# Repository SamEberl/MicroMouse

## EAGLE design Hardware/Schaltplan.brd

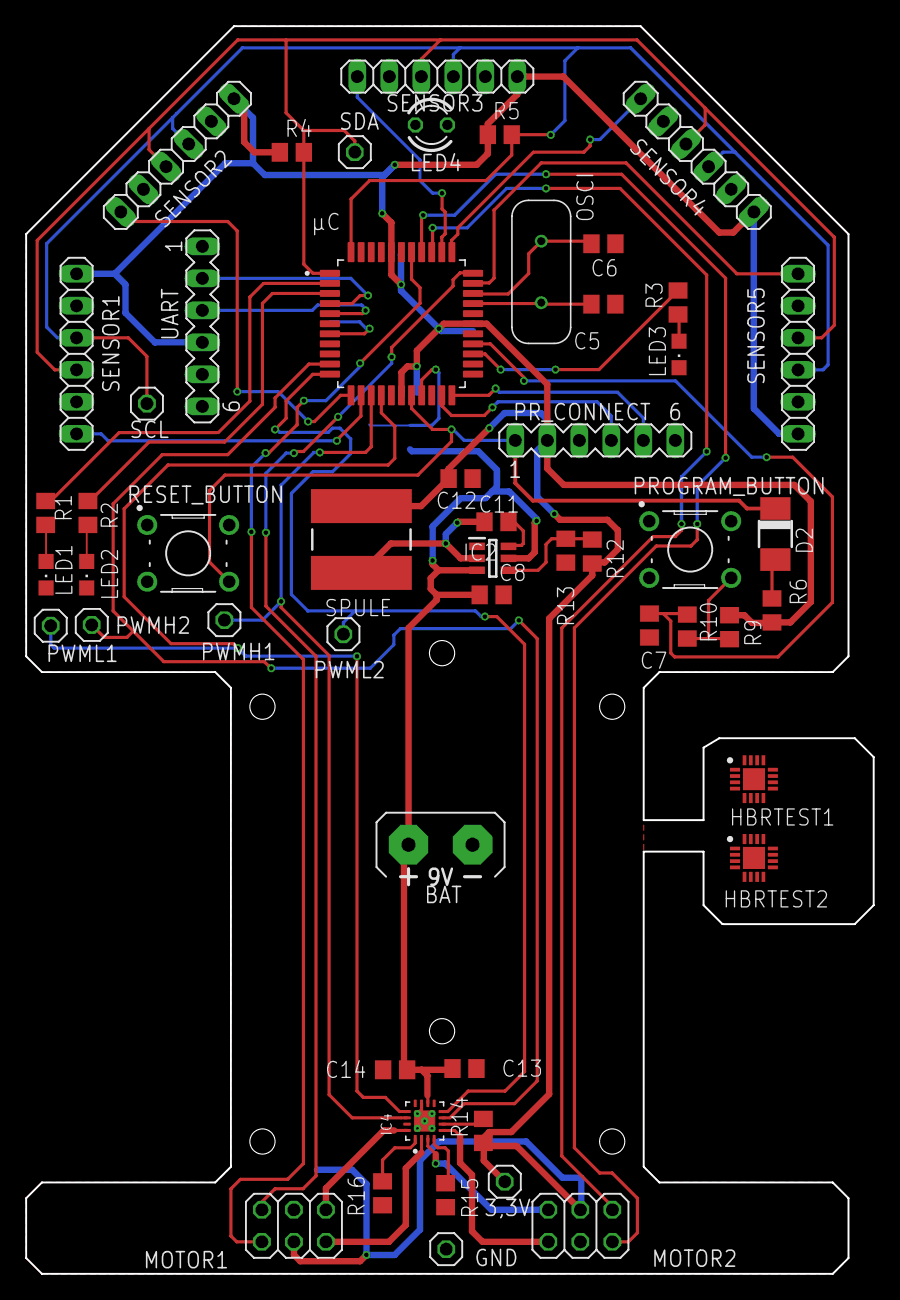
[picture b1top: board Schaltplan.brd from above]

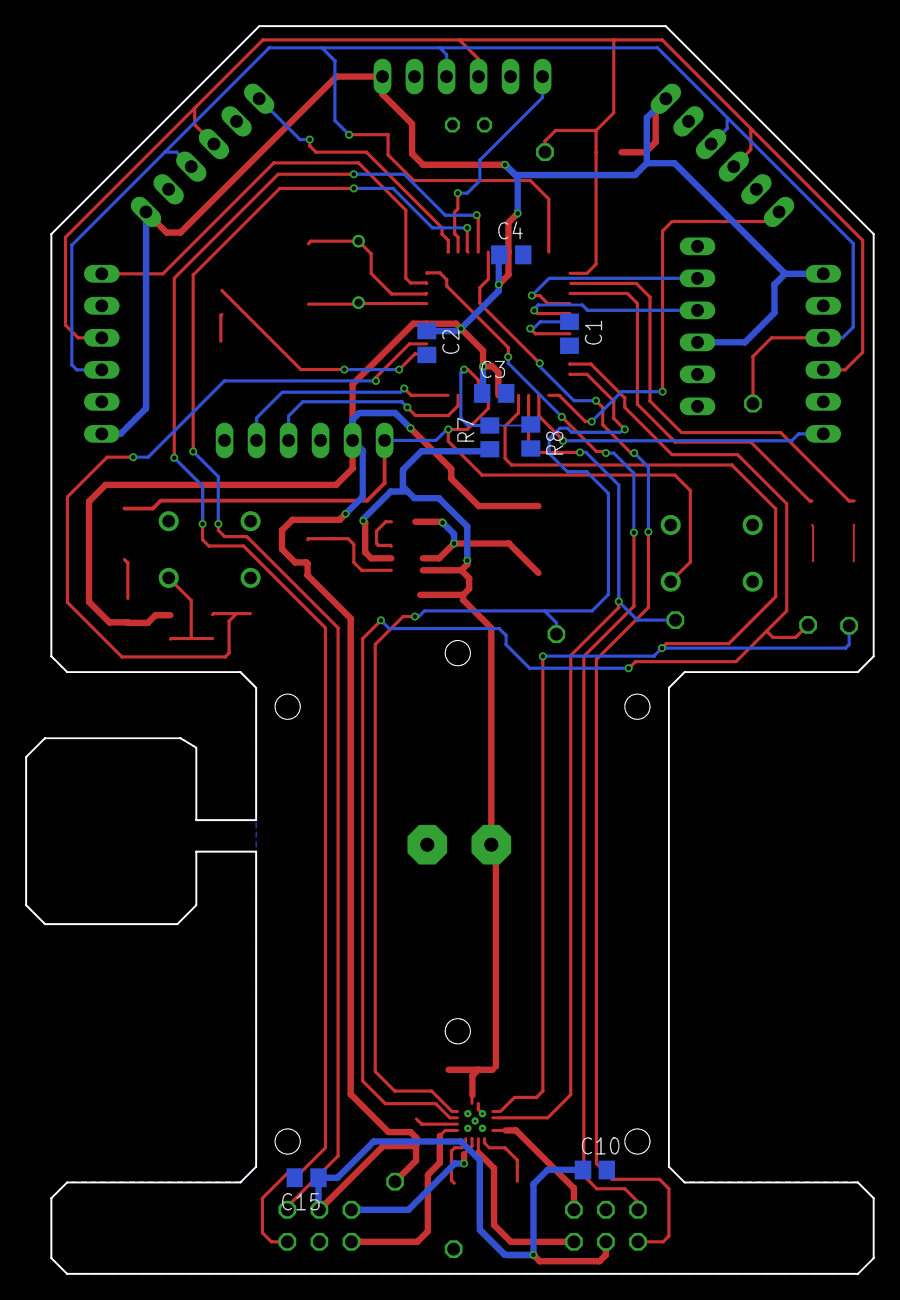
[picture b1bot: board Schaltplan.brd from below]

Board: 2 copper layers, 67.2 x 99.0 mm, 61 parts (8 on the bottom side), 46 nets.

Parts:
3,3V: 1X01
BAT: AB9V
C1: 10μ; C0805
C2, C3, C4: 0,1 μF; C0805
C5, C6: 15pf; C0805
C7: 1 µF; C0805
C8: 2.2 µF; C0805
C10, C14, C15: 100 nF; C0805
C11: 0,1 µF; C0805
C12: 44 µF; C0805
C13: 10 µF; C0805
D2: DO-214AC
GND: 1X01
HBRTEST1, HBRTEST2: DRV8411RTER; QFN50P300X300X80-17N
IC2: LMR51420XDDCR; SOT95P280X110-6N
IC4: DRV8411RTER; QFN50P300X300X80-17N
LED1, LED2, LED3: CHIPLED_0805
LED4: TLLR4400; LED3MM
MOTOR1, MOTOR2: 2X03
OSCI: ECS-160-20-4X-B-DN; XTAL_ECS-160-20-4X-B-DN
PROGRAM_BUTTON: B3F-1000; SW_B3F-1000
PR_CONNECT: MA06-1
PWMH1, PWMH2: 1X01
PWML1, PWML2: 1X01
R1, R2, R3: 680 Ω; R0805
R4, R5, R6, R8, R9, R14: 10 kΩ; R0805
R7: 20 kΩ; R0805
R10: 1kΩ; R0805
R12: 100 kΩ; R0805
R13: 22,1 kΩ; R0805
R15, R16: 1 Ω; R0805
RESET_BUTTON: B3F-1000; SW_B3F-1000
SCL: 1X01
SDA: 1X01
SENSOR1, SENSOR2, SENSOR3, SENSOR4, SENSOR5: 1X06
SPULE: SDR0805-6R8ML; SDR08056R8ML
UART: MA06-1
µC: DSPIC33FJ64MC804-I/PT; QFP80P1200X1200X120-44N

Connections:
3,3V: 3,3V.1, C2.1, C3.1, C4.1, C10.1, C12.1, C15.1, MOTOR1.4, MOTOR2.4, PR_CONNECT.2, R4.1, R5.1, R6.2, R9.2, R12.1, R14.1, SENSOR1.1, SENSOR2.1, SENSOR3.1, SENSOR4.1, SENSOR5.1, SPULE.2, UART.4, µC.17, µC.28, µC.40
9V: BAT.+, C8.1, C13.1, C14.2, IC2.3, IC2.5, IC4.10, R7.1
CRY1: C5.2, OSCI.1, µC.30
CRY2: C6.2, OSCI.2, µC.31
GND: BAT.-, C1.2, C2.2, C3.2, C4.2, C5.1, C6.1, C7.2, C8.2, C10.2, C12.2, C13.2, C14.1, C15.2, GND.1, IC2.1, IC4.11, IC4.17, IC4.18, IC4.19, IC4.20, IC4.21, IC4.22, LED1.C, LED2.C, LED3.C, LED4.A, LED4.K, MOTOR1.3, MOTOR2.3, PROGRAM_BUTTON.1, PROGRAM_BUTTON.2, PR_CONNECT.3, R8.2, R13.2, R15.2, R16.2, RESET_BUTTON.1, RESET_BUTTON.2, SENSOR1.2, SENSOR2.2, SENSOR3.2, SENSOR4.2, SENSOR5.2, UART.1, UART.6, µC.6, µC.16, µC.29, µC.39
GPIO0_1: SENSOR1.6, µC.13
GPIO0_2: SENSOR2.6, µC.12
GPIO0_3: SENSOR3.6, µC.35
GPIO0_4: SENSOR4.6, µC.34
GPIO0_5: SENSOR5.6, µC.32
KANAL1_A: MOTOR2.6, µC.36
KANAL1_B: MOTOR2.5, µC.37
KANAL2_A: MOTOR1.6, µC.38
KANAL2_B: MOTOR1.5, µC.33
LED1: R1.2, µC.2
LED2: R2.2, µC.3
LED3: R3.2, µC.25
M1+: IC4.2, MOTOR1.2
M1-: IC4.16, MOTOR1.1
M2+: IC4.3, MOTOR2.2
M2-: IC4.5, MOTOR2.1
MCLR: D2.C, PR_CONNECT.1, RESET_BUTTON.4, µC.18
unnamed: C1.1, µC.7
unnamed: PROGRAM_BUTTON.4, R9.1, R10.2
unnamed: LED2.A, R2.1
unnamed: LED1.A, R1.1
unnamed: C11.2, IC2.6
unnamed: LED3.A, R3.1
unnamed: D2.A, R6.1
unnamed: C11.1, IC2.2, SPULE.1
unnamed: IC4.6, R14.2
unnamed: IC2.4, R12.2, R13.1
unnamed: IC4.1, R16.1
unnamed: IC4.4, R15.1
PGC1: PR_CONNECT.5, µC.22
PGD1: PR_CONNECT.4, µC.21
PWMH1: IC4.14, PWMH1.1, µC.14
PWMH2: IC4.7, PWMH2.1, µC.10
PWML1: IC4.13, PWML1.1, µC.15
PWML2: IC4.8, PWML2.1, µC.11
SCL: R5.2, SCL.1, SENSOR1.3, SENSOR2.3, SENSOR3.3, SENSOR4.3, SENSOR5.3, µC.44
SDA: R4.2, SDA.1, SENSOR1.4, SENSOR2.4, SENSOR3.4, SENSOR4.4, SENSOR5.4, µC.1
SW1: C7.1, R10.1, µC.26
UART_RX: UART.2, µC.4
UART_TX: UART.3, µC.5
VREF: R7.2, R8.1, µC.19

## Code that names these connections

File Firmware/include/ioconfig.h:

/* 
 * File:   IOconfig.h
 * Author: adamp
 *
 * Created on 13 December 2019, 09:38
 */

#ifndef IOCONFIG_H
#define	IOCONFIG_H

#include "io_public.h"
#include "general.h"
#include "xc.h"

#define SEN1 LATAbits.LATA7
#define SEN2 LATAbits.LATA10
#define SEN3 LATAbits.LATA9
#define SEN4 LATAbits.LATA4
#define SEN5 LATAbits.LATA8

#define LED1 LATCbits.LATC6
#define LED2 LATCbits.LATC7
#define LED3 LATCbits.LATC0

#define SW1 PORTCbits.RC1

#define SW_PRESSED 0
#define SW_RELEASED 1

#define LEDOFF 0
#define LEDON 1
#define SENON 1
#define SENOFF 0

void setupIO();
void IO_10ms();
errorCode changeLEDState(uint8_t ledNr, uint8_t state);
errorCode IO_registerButtonPressedCB(ButtonPressedCB callback);
errorCode IO_registerButtonReleasedCB(ButtonReleasedCB callback);

#endif	/* IOCONFIG_H */

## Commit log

2023-01-17 Add planning folder
2023-01-29 setup simulation
2023-01-29 setup gitignore
2023-02-18 Schaltplan
2023-03-08 add .stl files for 3D print
2023-03-08 move into hardware folder
2023-03-23 tighter bat fit, larger screw holes
2023-04-13 commit current state to make fundamental changes to update position
2023-04-13 updated robot and sensor movement
2023-04-16 Firmware V0.1
2023-04-16 Disable UART for Testing
2023-04-17 commit to save legacy functions
2023-04-17 sensor returns right distance & pruning of files
2023-04-26 commit current state to check out other branch
2023-04-26 update gitignore
2023-04-26 added localization from sensor values
2023-04-27 Firmware V0.2
2023-04-29 add localization for robot
2023-04-30 fixed bugs in SLAM, added wall_width
2023-04-30 started PID controlling the angle
2023-05-02 added path planning, code messy but works
2023-05-02 separated parameters for easier access
2023-05-03 fixed minor issus
2023-05-06 mouse checks for faster path
2023-05-06 cleaned up code
2023-05-10 shortened code for localization
2023-05-10 remove redundant file
2023-05-13 quick commit to checkout other branch
2023-05-13 commented out things
2023-05-13 Add Scripts and environment.yml
2023-05-13 fixed seeing opposite wall because of noise
2023-05-13 renamed folder
2023-05-30 minor changes
2023-05-30 added software
2023-06-19 continued rewriting code from c++ to c
2023-06-19 rewriting c++ into c
2023-06-26 implemented queues in c
2023-06-26 implemented stack in c
2023-06-26 started making code useable for mplab
